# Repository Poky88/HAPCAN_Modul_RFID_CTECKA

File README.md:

# HAPCAN Extension Module - NFC Tag Reader

This repository contains complete hardware and software resources for the development and implementation of a new extension module for the HAPCAN home automation system. The module enables contactless user identification using RFID technology and subsequent control of smart home output elements via the CAN bus. This project was created as part of a bachelor's thesis.

<p align="center">
  
  <br>
  <i>Fig. 1: Module - 3D visualization</i>
</p>

## Features
- <ins>Contactless control:</ins> Output actuator control using RFID technology
- <ins>Access management:</ins> Setting access rights via the official HAPCAN Programmer application
- <ins>Universal output:</ins> Ability to control any actuator operating at 24 V
- <ins>Easy installation:</ins> Housed in a protective enclosure for standard in-wall flush-mount electrical boxes
- <ins>Connection options:</ins> The module can be connected to the CAN bus using an RJ45 connector or a screw terminal block
- <ins>Full compatibility:</ins> The device respects the HAPCAN protocol and communicates seamlessly with it
- <ins>Tag indication:</ins> Indicator LEDs signal when a tag is scanned

# Hardware
The schematic design and printed circuit board (PCB) layout were created using KiCad. All project source files and complete manufacturing files are available in the respective folders.

| PCB Model - TOP | PCB Model - BOT |
| :---: | :---: |
|  | |
<p align="center">
  <i> Fig. 2: PCB module visualization </i>
</p>

# Software

The complete firmware was developed in the Arduino IDE environment and is divided into two main parts. The operation of the NFC reader is handled by the `Hapcan_NFC.cpp` source file. CAN bus communication, module configuration, and interaction with the Hapcan Programmer application are managed by the second source file, `HapcanProtocol.cpp`. Both parts include corresponding header files for function declarations and library imports. To help understand the core program logic, flowchart diagrams of both main processes are provided below. The complete source codes are located in the attached folder.

<p align="center">
  
  <br>
  <i>Fig. 3: Flowchart - NFC Reader Operation</i>
</p>

<p align="center">
  
  <br>
  <i>Fig. 4: Flowchart - HAPCAN Protocol Operation</i>
</p>

# Module Construction

The complete module is housed inside a custom-designed protective enclosure. This case serves not only a protective function but also secures the NFC reader in the optimal position for reliable tag scanning. The fully assembled module is designed for easy mounting into a standard flush-mount in-wall electrical box. A detailed assembly and installation guide is described in the attached documentation, and the 3D models required for manufacturing the enclosure are included in the electronic appendices of the thesis. 

The following diagram illustrates an example wiring diagram using an electric lock. For correct operation, the module must be connected to the CAN bus and linked with a Button module.

<p align="center">

  <br>
  <i>Fig. 5: Typical wiring diagram</i>
</p>

<p align="center">
  
  <br>
  <i>Fig. 6: Assembled module</i>
</p>

# File Structure

<pre>
Hardware
└── KiCad 9.0                  # PCB design projects
    ├── production
    ├── Module - DPS.kicad_pcb
    ├── Module - DPS.kicad_pro
    └── Module - DPS.kicad_sch
Software
└── Arduino IDE 2.3.8          # Firmware source files
    └── HAPCAN
        ├── HAPCAN.ino
        ├── HAPCAN_NFC.cpp
        ├── HAPCAN_NFC.h
        ├── HAPCANProtocol.cpp
        └── HAPCANProtocol.h
3D printing
└── Inventor 2026              # 3D model of the protective enclosure
    ├── Cover - top part.ipt
    ├── Cover - assembly.iam
    └── Cover - bottom.ipt

Documentacion                  # PDF documentation of the module
    └── Documentation.pdf
</pre>

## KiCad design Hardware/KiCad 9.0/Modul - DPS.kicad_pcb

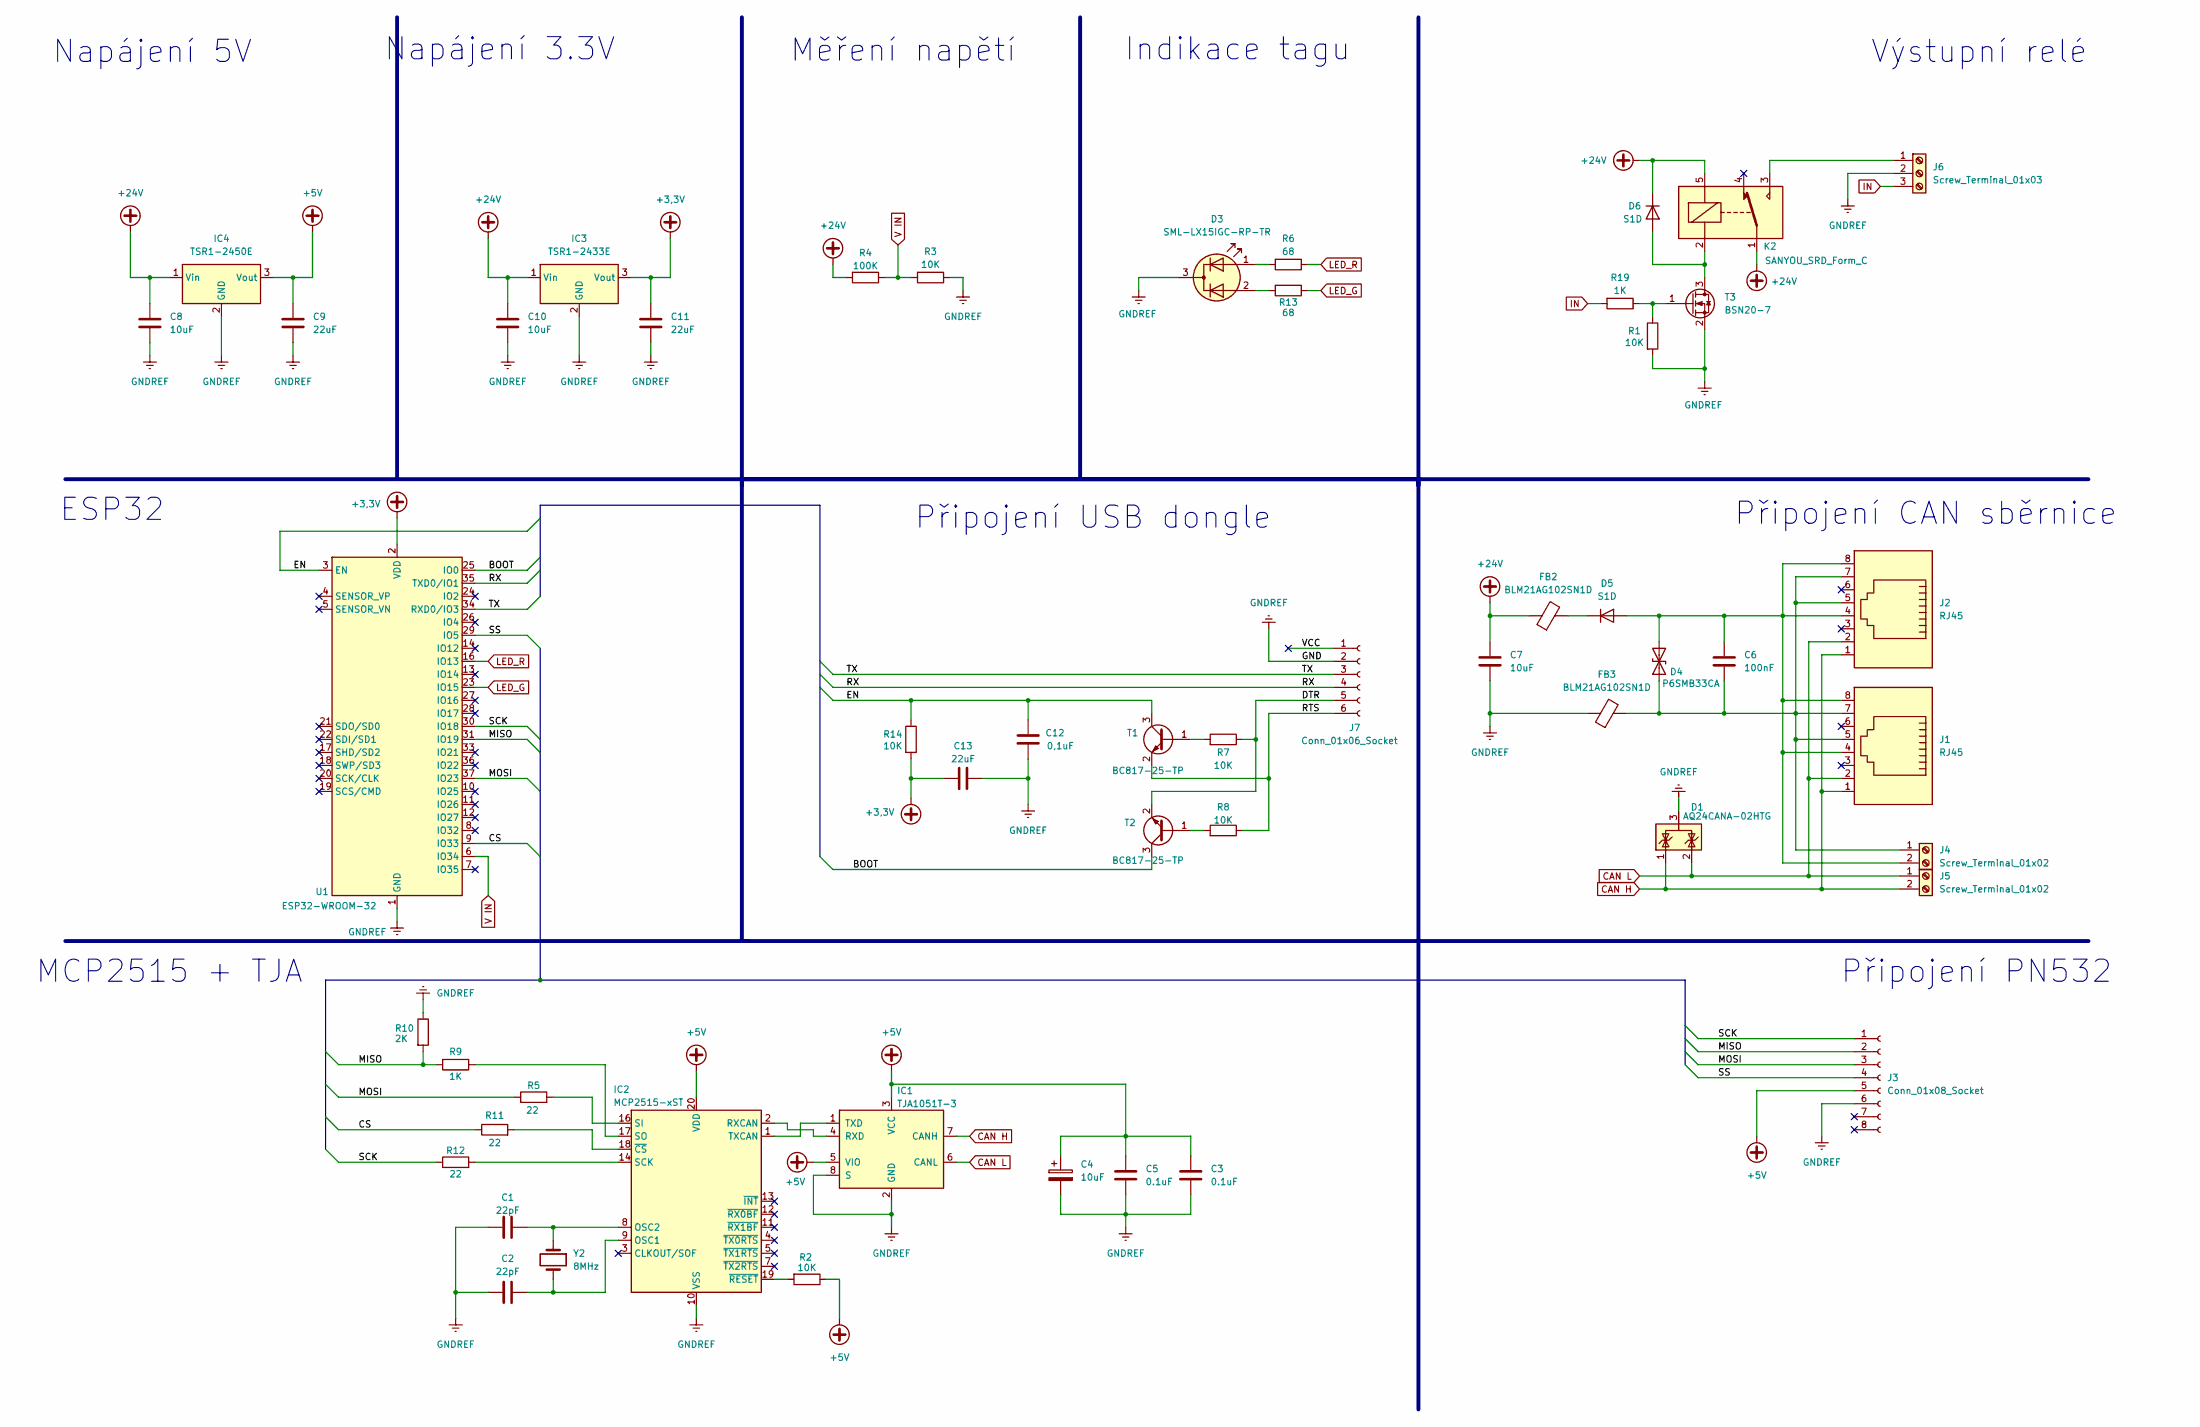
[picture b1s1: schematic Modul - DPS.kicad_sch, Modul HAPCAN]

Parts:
C1, C2: 22pF; C_0805_2012Metric_Pad1.18x1.45mm_HandSolder
C3, C5: 0.1uF; C_0805_2012Metric_Pad1.18x1.45mm_HandSolder
C4, C7, C8, C10: 10uF; C_1206_3216Metric_Pad1.33x1.80mm_HandSolder
C6: 100nF; C_0805_2012Metric_Pad1.18x1.45mm_HandSolder
C9, C11, C13: 22uF; C_0805_2012Metric_Pad1.18x1.45mm_HandSolder
C12: 0,1uF; C_0805_2012Metric_Pad1.18x1.45mm_HandSolder
D1: AQ24CANA-02HTG; SC-59_Handsoldering
D3: SML-LX15IGC-RP-TR; SOT-23-3
D4: P6SMB33CA; D_SMA_Handsoldering
D5, D6: S1D; D_SMA_Handsoldering
FB2, FB3: BLM21AG102SN1D; L_0805_2012Metric
IC1: TJA1051T-3; SOIC-8_3.9x4.9mm_P1.27mm
IC2: MCP2515-xST; TSSOP-20_4.4x6.5mm_P0.65mm
IC3: TSR1-2433E; Converter_DCDC_TRACO_TSR1-xxxxE_THT
IC4: TSR1-2450E; Converter_DCDC_TRACO_TSR1-xxxxE_THT
J1, J2: RJ45; RJ45_Amphenol_RJHSE5380
J3: Conn_01x08_Socket; PinSocket_1x08_P2.54mm_Vertical
J4, J5: Screw_Terminal_01x02; TerminalBlock_MaiXu_MX126-5.0-02P_1x02_P5.00mm
J6: Screw_Terminal_01x03; TerminalBlock_MaiXu_MX126-5.0-03P_1x03_P5.00mm
J7: Conn_01x06_Socket; PinSocket_1x06_P2.54mm_Vertical
K2: SANYOU_SRD_Form_C; Relay_SPDT_SANYOU_SRD_Series_Form_C
R1, R2, R3, R7, R8, R14: 10K; R_0805_2012Metric_Pad1.20x1.40mm_HandSolder
R4: 100K; R_0805_2012Metric_Pad1.20x1.40mm_HandSolder
R5, R11, R12: 22; R_0805_2012Metric_Pad1.20x1.40mm_HandSolder
R6, R13: 68; R_0805_2012Metric_Pad1.20x1.40mm_HandSolder
R9, R19: 1K; R_0805_2012Metric_Pad1.20x1.40mm_HandSolder
R10: 2K; R_0805_2012Metric_Pad1.20x1.40mm_HandSolder
T1, T2: BC817-25-TP; SOT-23
T3: BSN20-7; SOT-23-3
U1: ESP32-WROOM-32
Y2: 8MHz; Crystal_SMD_HC49-SD

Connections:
+3,3V: C11.1, C13.2, IC3.3 (Vout), R14.2, U1.2 (VDD)
+5V: C3.2, C4.1, C5.2, C9.1, IC1.3 (VCC), IC1.5 (VIO), IC2.20 (VDD), IC4.3 (Vout), J3.5, R2.1
+24V: C7.1, C8.1, C10.1, D6.1 (K), FB2.1, IC3.1 (Vin), IC4.1 (Vin), K2.1, K2.5, R4.2
/BOOT: T2.3 (C), U1.25 (IO0)
/CS: R11.1, U1.9 (IO33)
/DTR: J7.5, R7.1, T2.2 (E)
/EN: C12.1, R14.1, T1.3 (C), U1.3 (EN)
/MISO: J3.2, R9.2, R10.2, U1.31 (IO19)
/MOSI: J3.3, R5.1, U1.37 (IO23)
/RTS: J7.6, R8.1, T1.2 (E)
/RX: J7.4, U1.35 (TXD0/IO1)
/SCK: J3.1, R12.1, U1.30 (IO18)
/SS: J3.4, U1.29 (IO5)
/TX: J7.3, U1.34 (RXD0/IO3)
/VCC: J7.1
CAN H: D1.1 (K), IC1.7 (CANH), J1.1, J2.1, J5.2
CAN L: D1.2 (K), IC1.6 (CANL), J1.2, J2.2, J5.1
GNDREF: C1.1, C2.1, C3.1, C4.2, C5.1, C7.2, C8.2, C9.2, C10.2, C11.2, C12.2, C13.1, D1.3 (A), D3.3 (K), FB3.1, IC1.2 (GND), IC1.8 (S), IC2.10 (VSS), IC3.2 (GND), IC4.2 (GND), J3.6, J6.2, J7.2, R1.2, R3.1, R10.1, T3.2 (S), U1.1 (GND), U1.15 (GND), U1.38 (GND), U1.39 (GND)
IN: J6.3, R19.2
LED_G: R13.1, U1.23 (IO15)
LED_R: R6.1, U1.16 (IO13)
unnamed: D3.1 (A1), R6.2
unnamed: D3.2 (A2), R13.2
unnamed: C6.2, D4.1 (A1), FB3.2, J1.5, J1.7, J2.5, J2.7, J4.1
unnamed: C6.1, D4.2 (A2), D5.2 (A), J1.4, J1.8, J2.4, J2.8, J4.2
unnamed: D5.1 (K), FB2.2
unnamed: D6.2 (A), K2.2, T3.3 (D)
unnamed: IC1.4 (RXD), IC2.2 (RXCAN)
unnamed: IC1.1 (TXD), IC2.1 (TXCAN)
unnamed: C2.2, IC2.9 (OSC1), Y2.2
unnamed: C1.2, IC2.8 (OSC2), Y2.1
unnamed: IC2.14 (SCK), R12.2
unnamed: IC2.16 (SI), R5.2
unnamed: IC2.17 (SO), R9.1
unnamed: IC2.18 (~CS), R11.2
unnamed: IC2.19 (~RESET), R2.2
unnamed: J6.1, K2.3
unnamed: R7.2, T1.1 (B)
unnamed: R8.2, T2.1 (B)
unnamed: R1.1, R19.1, T3.1 (G)
V IN: R3.2, R4.1, U1.6 (IO34)

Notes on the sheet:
Indikace tagu
Připojení CAN sběrnice
Připojení USB dongle
Připojení PN532
Měření napětí
MCP2515 + TJA
Výstupní relé
Napájení 3.3V
ESP32
Napájení 5V

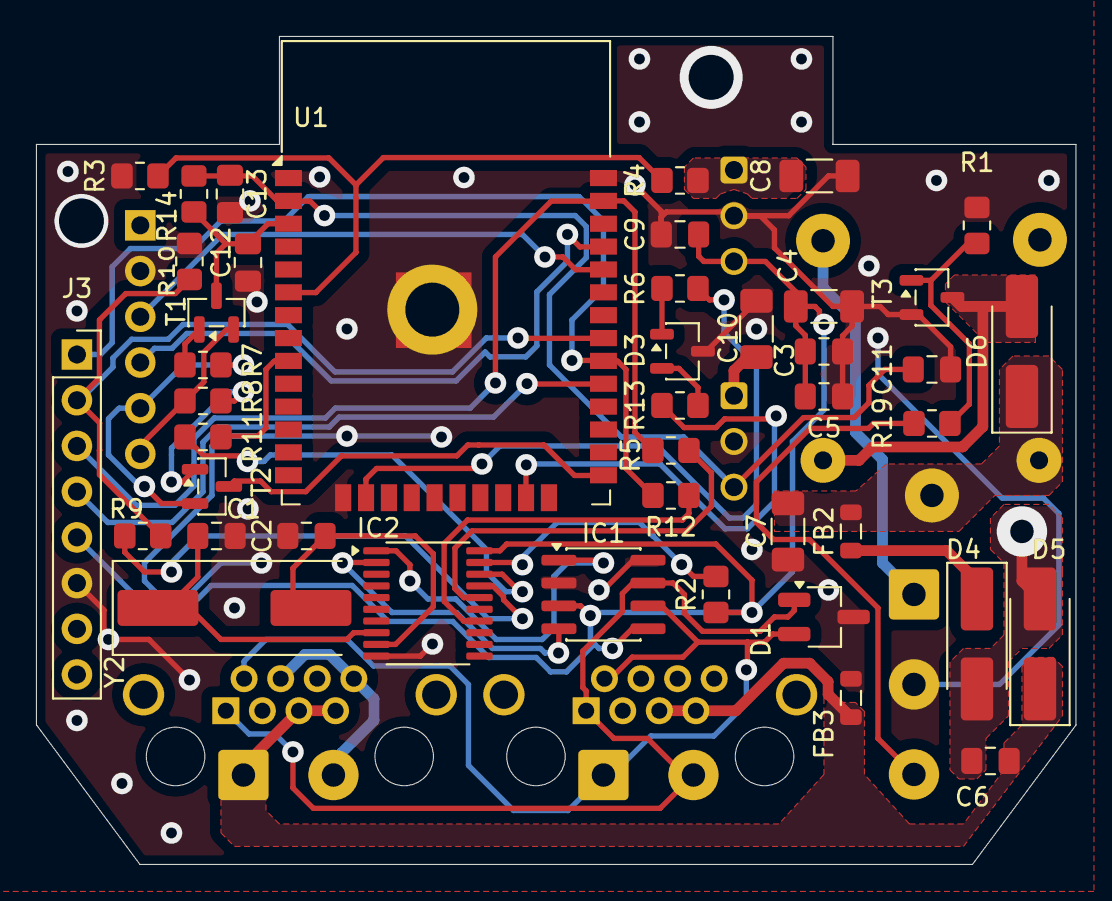
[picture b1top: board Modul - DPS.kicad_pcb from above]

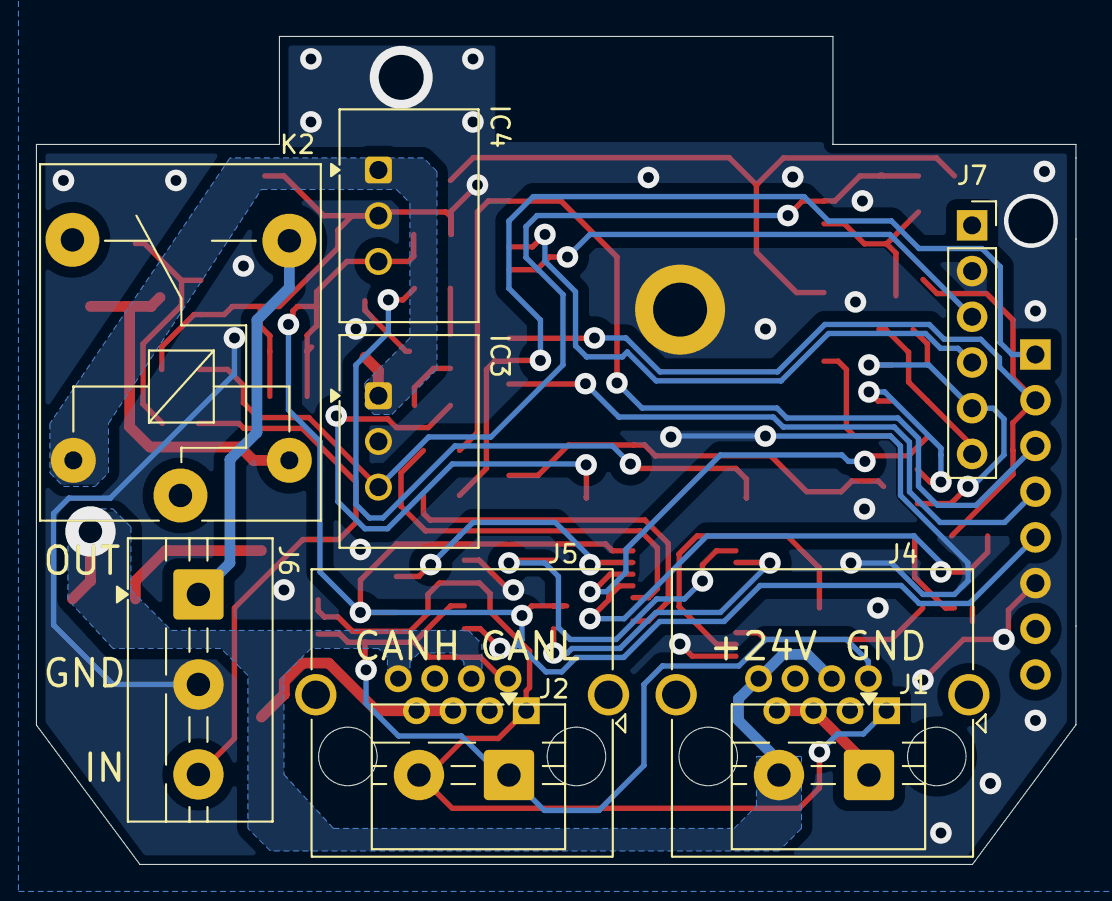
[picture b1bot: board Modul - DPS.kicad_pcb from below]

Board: 2 copper layers, 57.8 x 46.0 mm, 52 parts (9 on the bottom side), 40 nets.

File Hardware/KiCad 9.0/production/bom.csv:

Designator,Footprint,Quantity,Value,LCSC Part #
"C1, C2",0805,2,22pF,
"C10, C4, C7, C8",1206,4,10uF,
"C11, C13, C9",0805,3,22uF,
C12,0805,1,"0,1uF",
"C3, C5",0805,2,0.1uF,
C6,0805,1,100nF,
D1,SC-59_Handsoldering,1,AQ24CANA-02HTG,
D3,SOT-23-3,1,SML-LX15IGC-RP-TR,
D4,D_SMA_Handsoldering,1,P6SMB33CA,
"D5, D6",D_SMA_Handsoldering,2,S1D,
"FB2, FB3",0805,2,BLM21AG102SN1D,
IC1,SOIC-8_3.9x4.9mm_P1.27mm,1,TJA1051T-3,
IC2,TSSOP-20_4.4x6.5mm_P0.65mm,1,MCP2515-xST,
IC3,Converter_DCDC_TRACO_TSR1-xxxxE_THT,1,TSR1-2433E,
IC4,Converter_DCDC_TRACO_TSR1-xxxxE_THT,1,TSR1-2450E,
"J1, J2",RJ45_Amphenol_RJHSE5380,2,RJ45,
J3,PinSocket_1x08_P2.54mm_Vertical,1,Conn_01x08_Socket,
"J4, J5",TerminalBlock_MaiXu_MX126-5.0-02P_1x02_P5.00mm,2,Screw_Terminal_01x02,
J6,TerminalBlock_MaiXu_MX126-5.0-03P_1x03_P5.00mm,1,Screw_Terminal_01x03,
J7,PinSocket_1x06_P2.54mm_Vertical,1,Conn_01x06_Socket,
K2,Relay_SPDT_SANYOU_SRD_Series_Form_C,1,SANYOU_SRD_Form_C,
"R1, R14, R2, R3, R7, R8",0805,6,10K,
R10,0805,1,2K,
"R11, R12, R5",0805,3,22,
"R13, R6",0805,2,68,
"R19, R9",0805,2,1K,
R4,0805,1,100K,
"T1, T2",SOT-23,2,BC817-25-TP,
T3,SOT-23-3,1,BSN20-7,
U1,ESP32-WROOM-32,1,ESP32-WROOM-32,
Y2,Crystal_SMD_HC49-SD,1,8MHz,

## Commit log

2026-03-24 Create README-md
2026-03-24 Create HARDWARE
2026-03-24 Rename README-md to README.md
